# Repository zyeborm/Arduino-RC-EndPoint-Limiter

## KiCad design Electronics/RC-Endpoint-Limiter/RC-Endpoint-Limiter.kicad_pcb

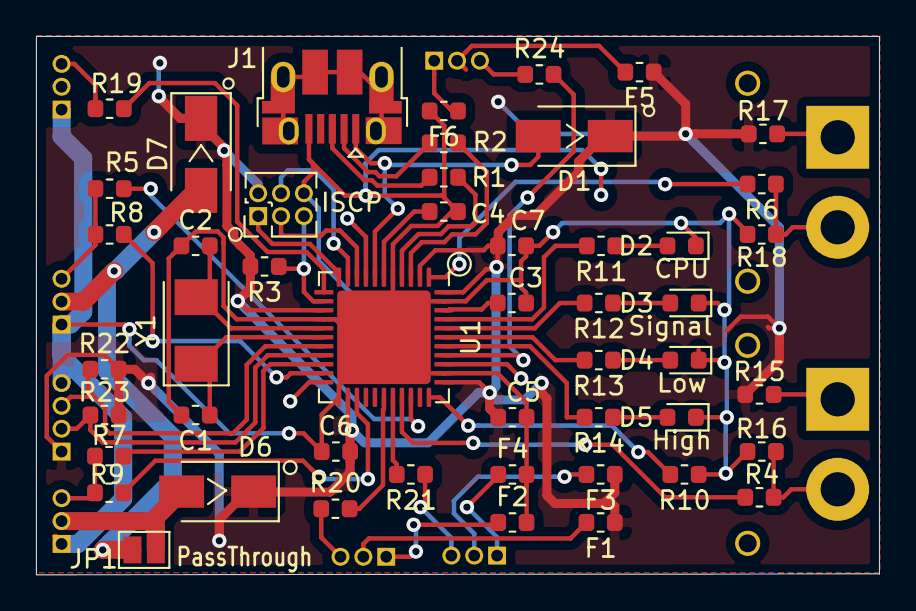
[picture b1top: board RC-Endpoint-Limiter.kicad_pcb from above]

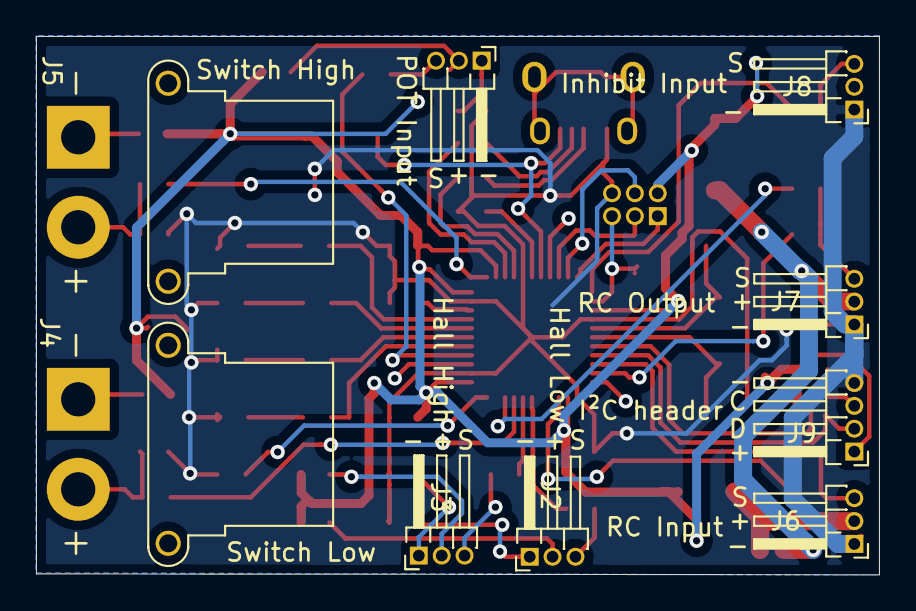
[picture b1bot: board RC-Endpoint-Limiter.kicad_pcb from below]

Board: 2 copper layers, 46.8 x 29.9 mm, 58 parts (9 on the bottom side), 54 nets.

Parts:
C1, C2: 22pf; C_0603_1608Metric
C3: 100n; C_0603_1608Metric
C4, C5, C6, C7: 1uF; C_0603_1608Metric
D1: USB Supply; D_SMA
D2: CPU; LED_0603_1608Metric
D3: Signal; LED_0603_1608Metric
D4: Low; LED_0603_1608Metric
D5: High; LED_0603_1608Metric
D6: Input Supply; D_SMA
D7: Output Supply; D_SMA
F1, F2, F3, F4, F5, F6: 0.5A; Fuse_0603_1608Metric
J1: USB_B_Micro; USB_Micro-B_Amphenol_10103594-0001LF_Horizontal
J2: Hall Low; PinHeader_1x03_P1.27mm_Horizontal
J3: Hall High; PinHeader_1x03_P1.27mm_Horizontal
J4: Switch Low; AMASS_XT30PW-F_1x02_P2.50mm_Horizontal
J5: Switch High; AMASS_XT30PW-F_1x02_P2.50mm_Horizontal
J6: RC Input; PinHeader_1x03_P1.27mm_Horizontal
J7: RC Output; PinHeader_1x03_P1.27mm_Horizontal
J8: Inhibit Input; PinHeader_1x03_P1.27mm_Horizontal
J9: I²C header; PinHeader_1x04_P1.27mm_Horizontal
J10: ISCP; PinHeader_2x03_P1.27mm_Vertical
J11: POT Input; PinHeader_1x03_P1.27mm_Horizontal
JP1: PassThrough; SolderJumper-2_P1.3mm_Open_Pad1.0x1.5mm
R1, R2: 22R; R_0603_1608Metric
R3, R10, R22, R23: 10K; R_0603_1608Metric
R4, R6, R7, R9, R16, R18, R19, R20, R21, R24: 1K; R_0603_1608Metric
R5, R8: 100R; R_0603_1608Metric
R11, R12, R13, R14, R15, R17: 240R; R_0603_1608Metric
U1: ATmega32U4-MU; QFN-44-1EP_7x7mm_P0.5mm_EP5.2x5.2mm
Y1: 8Mhz; Crystal_SMD_5032-2Pin_5.0x3.2mm

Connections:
/MISO: J10.1, U1.11
/MOSI: J10.4, U1.10
/RESET: J10.5, R3.1, U1.13
/SCK: J10.3, U1.9
GND: C1.2, C2.1, C3.2, C4.2, C5.1, C6.1, C7.1, D2.1, D3.1, D4.1, D5.1, F2.2, F4.2, F6.2, J1.5, J6.1, J7.1, J8.1, J9.4, J10.6, R10.1, R16.1, R18.1, U1.5, U1.15, U1.23, U1.35, U1.43, U1.45
unnamed: C1.1, U1.17, Y1.1
unnamed: C2.2, U1.16, Y1.2
unnamed: C3.1, U1.42
unnamed: C4.1, U1.6
unnamed: D1.2, J1.1, U1.7
unnamed: D2.2, R11.1
unnamed: D3.2, R12.1
unnamed: D4.2, R13.1
unnamed: D5.2, R14.1
unnamed: D6.2, J6.2, JP1.2
unnamed: D7.2, J7.2, JP1.1
unnamed: F1.2, J2.2
unnamed: F2.1, J2.1
unnamed: F3.2, J3.2
unnamed: F4.1, J3.1
unnamed: F5.2, J11.2
unnamed: F6.1, J11.1
unnamed: J1.2, R2.2
unnamed: J1.3, R1.2
unnamed: J2.3, R20.1
unnamed: J3.3, R21.1
unnamed: J4.1, R15.1
unnamed: J4.2, R4.1, R16.2
unnamed: J5.1, R17.1
unnamed: J5.2, R6.1, R18.2
unnamed: J6.3, R7.1, R9.1
unnamed: J7.3, R5.1, R8.1
unnamed: J8.3, R19.1
unnamed: J9.2, R23.1, U1.19
unnamed: J9.3, R22.1, U1.18
unnamed: J11.3, R24.1
unnamed: R1.1, U1.4
unnamed: R2.1, U1.3
unnamed: R4.2, U1.30
unnamed: R5.2, U1.31
unnamed: R6.2, U1.1
unnamed: R7.2, U1.20
unnamed: R8.2, U1.21
unnamed: R9.2, U1.25
unnamed: R10.2, U1.33
unnamed: R11.2, U1.41
unnamed: R12.2, U1.40
unnamed: R13.2, U1.39
unnamed: R14.2, U1.38
unnamed: R19.2, U1.12
unnamed: R20.2, U1.28
unnamed: R21.2, U1.29
unnamed: R24.2, U1.37
VCC: C5.2, C6.2, C7.2, D1.1, D6.1, D7.1, F1.1, F3.1, F5.1, J9.1, J10.2, R3.2, R15.2, R17.2, R22.2, R23.2, U1.2, U1.14, U1.24, U1.34, U1.44

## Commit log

2018-07-30 create blank
2018-07-30 copied rc burket
    copied rc burket as a base
2018-12-11 moved stuff to organise the repo a bit
2018-12-12 started defs
2018-12-12 draft defs finished
2019-06-16 Update Arduino_RC_EndPoint_Limiter.ino
    setup started
2019-06-24 ISR for switch detect added but not working
2019-06-24 Update Arduino_RC_EndPoint_Limiter.ino
    Low and high interrupt driven LED's are working
2019-06-25 almost working
2019-06-25 Update Arduino_RC_EndPoint_Limiter.ino
    First fuctional version
2019-07-01 Made limit indicator LED's flash when signal good and switch pressed to show output is being limited
2019-07-01 altered zero pulse and out of safe range pulse during startup message
    added serial flush during startup
    added setup function stub
2019-07-04 Prepared for eeprom storage of settings by creating a "settings" struct and a function to reset that to defaults. Presently not actually storing and just calling the reset at the start of setup but i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
2019-07-08 set CenterPointInputMin and CenterPointInputMax to sane defaults Added eeprom read, and setting defaults if it's blank not doing validation yet
2019-07-08 Started conversion to println(String) rather than lots of seperate print statements, probably going to use more of the string stuff doing the UI for the getting eeprom values over serial anyway
2019-07-10 Added parseint for recieving settings realised the println(string) uses up heaps of global variables for every occourance will need to take that back out :-(
2019-07-18 ITS ALIVE! Added power cycle counter as 32bit unsigned because reasons Added saving of settings to eeprom tidied settings savings code
    realised it should print settings at boot so will need to gut that out of settings savings code
    need to take out some (string) and go back to printlns
    should lint and style it all consistently
    status flashing goes solid on bad signal which means it just looks dead, need to do something better there
    need to implement output disable on bad/no signal.
2019-07-24 Added servo output disable on loss of signal. removed all (string) tidied up a bit
    still needs linting.
2019-08-04 Started electronics
2019-08-05 added usb port connections decided on smt crystal for usb operation, they seem robust enough
2019-08-11 Update Arduino_RC_EndPoint_Limiter.ino
    fixed bug where signal good pulses was fixed at 10 rather than using signal limit in the main loop.
    Fixed a typo and added comment for what ascii 83 is. (s)
2019-08-31 schematic entered no hardware capture is going to be supported for RC in as it's not shared with any interrupt pins and I want to play it safe there might use timer3 for RC output but the update dela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
2019-09-01 polished electornics
2019-09-01 started component assignment
2019-09-02 component allocation
2019-09-14 first draft PCB
2019-09-16 made aux inputs dedicated hall inputs, Make sure to enable pullups, bit low on board space around there to fit external pullup resistors added fuses.
2019-09-17 added lots more I/O
2019-09-21 polished up PCB layout
